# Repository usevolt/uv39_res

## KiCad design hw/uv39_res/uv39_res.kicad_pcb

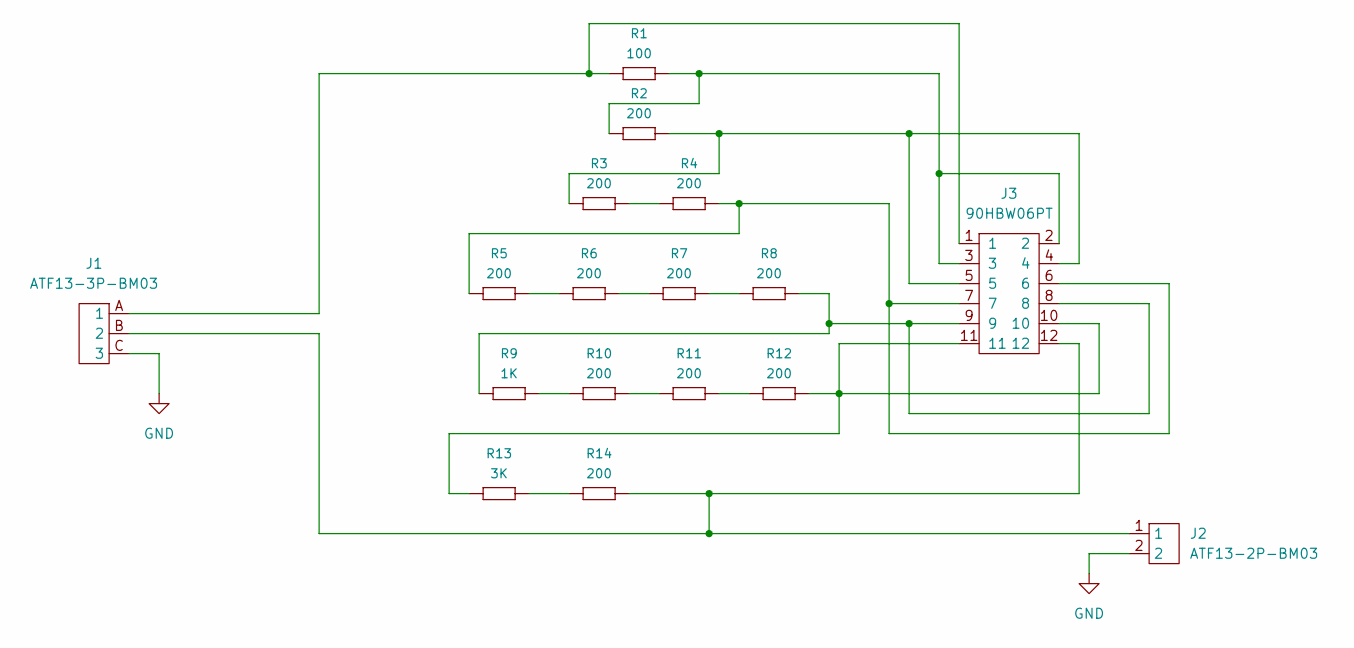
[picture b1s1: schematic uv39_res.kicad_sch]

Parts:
J1: ATF13-3P-BM03; Manufacturer part number ATF13-3P-BM03
J2: ATF13-2P-BM03; Manufacturer part number ATF13-2P-BM03
J3: 90HBW06PT; Manufacturer Part Number 90HBW06PT
R1: 100; 0603; Manufacturer Part Number MC0063W06031100R
R2, R3, R4, R5, R6, R7, R8, R10, R11, R12, R14: 200; 0603; Manufacturer Part Number MC0063W06031200R
R9: 1K; 0603; Manufacturer Part Number MC0063W060311K
R13: 3K; 0603; Manufacturer Part Number MC0063W060313K

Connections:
GND: J1.C (3), J2.2
unnamed: J1.A (1), J3.1, R1.2 (R2)
unnamed: J1.B (2), J2.1, J3.12, R14.1 (R1)
unnamed: J3.2, J3.3, R1.1 (R1), R2.2 (R2)
unnamed: J3.4, J3.5, R2.1 (R1), R3.2 (R2)
unnamed: R3.1 (R1), R4.2 (R2)
unnamed: J3.6, J3.7, R4.1 (R1), R5.2 (R2)
unnamed: R5.1 (R1), R6.2 (R2)
unnamed: R6.1 (R1), R7.2 (R2)
unnamed: R7.1 (R1), R8.2 (R2)
unnamed: J3.8, J3.9, R8.1 (R1), R9.2 (R2)
unnamed: R10.1 (R1), R11.2 (R2)
unnamed: R9.1 (R1), R10.2 (R2)
unnamed: R11.1 (R1), R12.2 (R2)
unnamed: J3.10, J3.11, R12.1 (R1), R13.2 (R2)
unnamed: R13.1 (R1), R14.2 (R2)

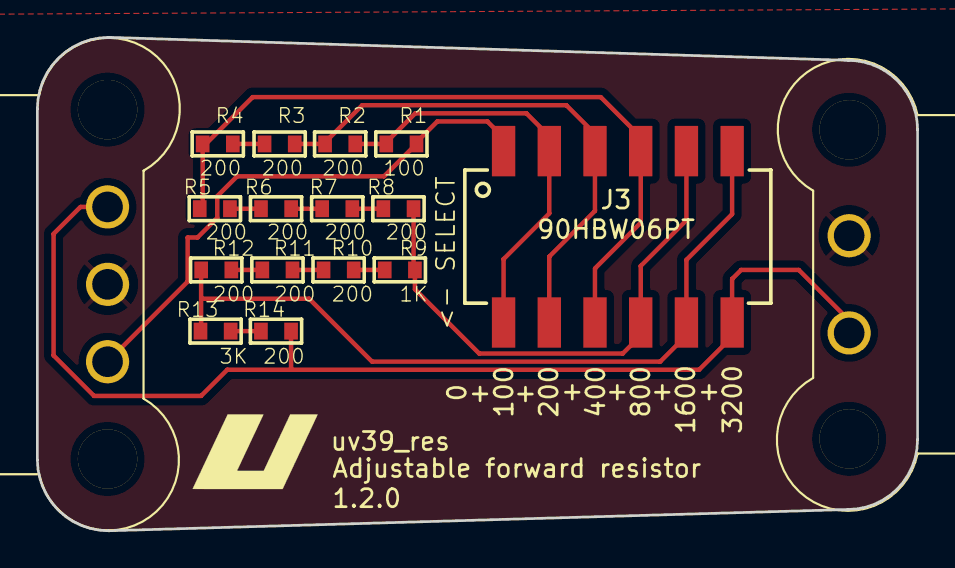
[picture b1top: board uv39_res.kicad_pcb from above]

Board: 2 copper layers, 48.9 x 27.4 mm, 17 parts (0 on the bottom side), 16 nets.

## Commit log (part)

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2025-10-18 initial version of adjustable resistor PCb
2025-10-18 lockfiles removed
2025-10-18 assembly directory created
2026-01-14 1.1.0 silkscreen fixes
2026-04-23 DT063S pin out fixed
